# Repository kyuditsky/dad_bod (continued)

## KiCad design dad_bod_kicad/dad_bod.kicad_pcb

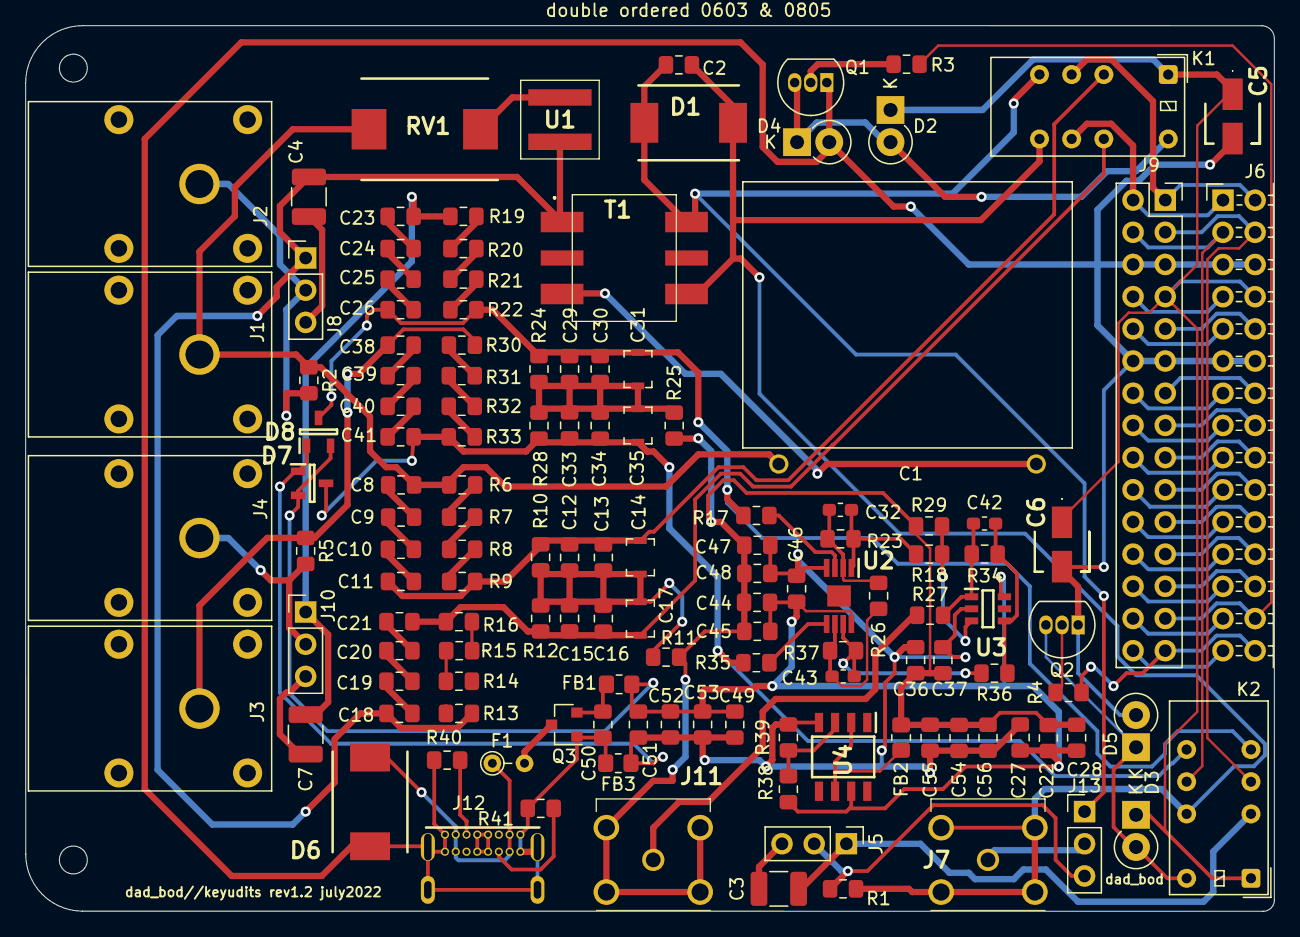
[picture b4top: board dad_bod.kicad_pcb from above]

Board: 2 copper layers, 98.5 x 69.9 mm, 133 parts (0 on the bottom side), 98 nets.

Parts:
C1: ECQ-UBAF474K; ECQ-UBAF474K-3_side
C2: 220pF; C_0805_2012Metric_Pad1.15x1.40mm_HandSolder
C3, C4, C7: 86nF; C_1210_3225Metric_Pad1.33x2.70mm_HandSolder
C5, C6: CP; EEE1AA220WR
C8, C9, C10, C11, C18, C19, C20, C21, C23, C24, C25, C26, C38, C39, C40, C41: 4pf; C_0805_2012Metric_Pad1.15x1.40mm_HandSolder
C12, C13, C15, C16, C29, C30, C33, C34: 350pF; C_0805_2012Metric_Pad1.15x1.40mm_HandSolder
C14, C17, C31, C35: CTRIM; C_Trimmer_Voltronics_JQ
C22, C27, C28, C36, C37, C44, C45, C46, C47, C48, C49, C50, C51, C52, C53, C54, C55, C56: C_0805_2012Metric_Pad1.15x1.40mm_HandSolder
C32, C42, C43: C_0603_1608Metric_Pad1.05x0.95mm_HandSolder
D1: SMCJ918.0CA; DIONM7959X262N
D2, D3, D4, D5: 1N4001; D_DO-41_SOD81_P2.54mm_Vertical_KathodeUp
D6: SMCJ5.0A; littlefuseTVS
D7, D8: BAV199-TP; bav199_tp_SOT95P237X125-3N
F1: 2.5a Fuse; R_Axial_DIN0204_L3.6mm_D1.6mm_P2.54mm_Vertical
FB1, FB2, FB3: Ferrite_Bead; R_0805_2012Metric_Pad1.20x1.40mm_HandSolder
J1, J2, J3, J4: Conn_01x01; Banana_Jack_S_RA_73099
J5, J8, J10, J13: Conn_01x03_Male; PinHeader_1x03_P2.54mm_Vertical
J6: Conn_02x15_Odd_Even; PinHeader_2x15_P2.54mm_Horizontal
J7, J11: BNC5-J-P-GN-RA-BH2D; BNC5JPGNRABH2D
J9: Conn_02x15_Odd_Even; PinSocket_2x15_P2.54mm_Vertical
J12: USB4085-GF-A_REVA4; GCT_USB4085-GF-A_REVA4
K1, K2: EC2-5NU; Relay_DPDT_Kemet_EC2
Q1, Q2: 2N3904; TO-92_Inline
Q3: AO3401A; SOT-23
R1, R2, R5: 30M; R_0805_2012Metric_Pad1.15x1.40mm_HandSolder
R3, R4: 1k; R_0805_2012Metric_Pad1.15x1.40mm_HandSolder
R6, R7, R8, R9, R13, R14, R15, R16, R19, R20, R21, R22, R30, R31, R32, R33: 1M; R_0805_2012Metric_Pad1.15x1.40mm_HandSolder
R10, R12, R24, R28: 50k; R_0805_2012Metric_Pad1.15x1.40mm_HandSolder
R11, R25: DNP; R_0805_2012Metric_Pad1.15x1.40mm_HandSolder
R17, R18, R23, R26, R27, R29, R34, R35, R36, R37, R38, R39: R_0805_2012Metric_Pad1.15x1.40mm_HandSolder
R40, R41: 5.1k; R_0805_2012Metric_Pad1.15x1.40mm_HandSolder
RV1: VP4032K122R300; CAPPM10080X500N
T1: GT07-110-013; GT07110013
U1: SL1002A600SP
U2: LTC6269; SOP65P490X110-9N_LTC6269
U3: LTC6268; SOT95P280X100-6N_LTC6268
U4: LM7301; SOIC127P600X175-8NLM7301

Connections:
0: J6.16, J9.15
1: J6.18, J9.17
2: J6.20, J9.19
3: J6.22, J9.21
4: J6.24, J9.23
5: J6.26, J9.25
8: J6.15, J9.16
9: J6.17, J9.18
10: J6.19, J9.20
11: J6.21, J9.22
12: J6.23, J9.24
13: J6.25, J9.26
14: J6.27, J9.28
15: J6.29, J9.30
BNCin+: C3.2, J5.1, K2.3
CV6: J6.28, J9.27, R3.1
CV7: J6.30, J9.29, R4.1
DIVin1+: C7.2, C23.2, J10.1, R19.1
DIVin1-: C38.1, J3.1, R5.1, R30.2
DIVout1+: C26.1, C29.2, C30.2, C31.1, D8.3 (A/K), K2.5, R17.2, R22.2, R24.2
DIVout1-: C33.1, C34.1, C35.2, C41.2, D7.3 (A/K), K2.8, R28.1, R33.1, R35.2
DIVout2+: C11.1, C12.2, C13.2, C14.1, K1.3, R9.2, R10.2
DIVout2-: C15.1, C16.1, C17.2, C21.2, K1.10, R12.1, R16.1
GND: C5.2, C6.2, C50.1, D4.2 (A), D5.2 (A), D6.2, FB3.2, J6.5, J6.6, J6.11, J6.12, J9.5, J9.6, J9.11, J9.12, J12.A1 (GND), J12.A12 (GND), J12.B1 (GND), J12.B12 (GND), J12.P1 (SHELL), J12.P2 (SHELL), J12.P3 (SHELL), J12.P4 (SHELL), Q1.1 (E), Q2.1 (E), Q3.1 (G), R40.1, R41.2
GNDREF: C22.1, C28.1, C36.1, C37.1, C44.2, C45.2, C47.2, C48.2, C54.2, C55.2, C56.2, FB2.1, J11.2, J11.3, J11.4, J11.5, R11.1, R25.1, R29.1
unnamed: C1.2, T1.3 (DRIVE_3)
unnamed: C3.1, J5.3
unnamed: C4.1, J8.3
unnamed: C7.1, J10.3
unnamed: C8.1, C9.2
unnamed: C10.1, C11.2
unnamed: C9.1, C10.2
unnamed: C12.1, C13.1, C14.2, C15.2, C16.2, C17.1, R10.1, R11.2, R12.2
unnamed: C18.2, C19.1
unnamed: C19.2, C20.1
unnamed: C20.2, C21.1
unnamed: C23.1, C24.2
unnamed: C24.1, C25.2
unnamed: C25.1, C26.2
unnamed: C29.1, C30.1, C31.2, C33.2, C34.2, C35.1, R24.1, R25.2, R28.2
unnamed: C32.1, R18.2, R23.1, U2.1
unnamed: C32.2, R23.2, R26.2, U2.2 (-)
unnamed: C38.2, C39.1
unnamed: C39.2, C40.1
unnamed: C40.2, C41.1
unnamed: C42.1, R27.2, R34.1, U3.1
unnamed: C42.2, R34.2, R36.1, U3.4 (-)
unnamed: C43.1, R36.2, R37.1, U2.7
unnamed: C43.2, R26.1, R37.2, U2.6 (-)
unnamed: C50.2, FB1.2, Q3.2 (S)
unnamed: D2.2 (A), D4.1 (K), K1.12, Q1.3 (C)
unnamed: D3.2 (A), D5.1 (K), K2.12, Q2.3 (C)
unnamed: D6.1, F1.1, J12.A4 (VBUS), J12.A9 (VBUS), J12.B4 (VBUS), J12.B9 (VBUS)
unnamed: FB2.2, U4.2 (-), U4.6
unnamed: J2.1, J8.2, R2.2
unnamed: J7.1, J13.2
unnamed: J4.1, J10.2, R5.2
unnamed: J11.1, R27.1
unnamed: J12.A5 (CC1), R40.2
unnamed: J12.A6 (DP1), J12.A7 (DN1), J12.B6 (DP2), J12.B7 (DN2)
unnamed: J12.B5 (CC2), R41.1
unnamed: Q1.2 (B), R3.2
unnamed: Q2.2 (B), R4.2
unnamed: R6.2, R7.1
unnamed: R7.2, R8.1
unnamed: R8.2, R9.1
unnamed: R13.1, R14.2
unnamed: R14.1, R15.2
unnamed: R15.1, R16.2
unnamed: R17.1, U2.3 (+)
unnamed: R18.1, R29.2, U3.3 (+)
unnamed: R19.2, R20.1
unnamed: R20.2, R21.1
unnamed: R21.2, R22.1
unnamed: R30.1, R31.2
unnamed: R31.1, R32.2
unnamed: R32.1, R33.2
unnamed: R35.1, U2.5 (+)
unnamed: R38.1, R39.1, U4.3 (+)
unnamed: RV1.1, U1.1
PLCin+: C4.2, C18.1, J8.1, R13.2, T1.1 (DRIVE_1), U1.2
PLCin-: C1.1, C8.2, J1.1, R2.1, R6.1, RV1.2
PLCout+: C2.2, D1.1, J13.1, K1.5, T1.6 (GATE_3)
PLCout-: C2.1, D1.2, J7.2, J7.3, J7.4, J7.5, K1.8, K2.10, R1.1, T1.4 (GATE_1)
V+: F1.2, Q3.3 (D)
VCC: C22.2, C27.1, C28.2, C44.1, C45.1, C46.2, C49.2, C51.2, C52.2, C53.2, D7.2 (K), D8.2 (K), FB1.1, R38.2, U2.8 (V+), U3.6 (V+), U4.7 (V+)
bnc_imp+: J5.2, J13.3, R1.2
dad_V-: J6.7, J9.8
greg: C27.2, C36.2, C37.2, C46.1, C47.1, C48.1, C49.1, C51.1, C52.1, C53.1, C54.1, C55.1, C56.1, D7.1 (A), D8.1 (A), FB3.1, R39.2, U2.4 (V-), U3.2 (V-), U4.4 (V-)
relaypwr: C5.1, C6.1, D2.1 (K), D3.1 (K), J6.8, J9.7, K1.1, K2.1
scope1+: J6.2, J9.1, K1.4
scope1-: J6.1, J9.2, K1.9
scope2+: J6.4, J9.3, K2.4
scope2-: J6.3, J9.4, K2.9
trigger1: J6.14, J9.13
trigger2: J6.13, J9.14
waveform1: J6.10, J9.9
waveform2: J6.9, J9.10

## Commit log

2022-02-11 Added readme.md & .gitignore
2022-02-11 Imported HPF, added divider, dad IO, & relay
2022-02-11 Corrected hpf scheme, added pass throughs on the dad io, changed j1/j2 inputs
2022-02-13 Reworked voltage divider, added attenuation simulation schematic
2022-02-23 Altered voltage divider section & added simulation circuit
2022-03-24 Added differential schematic & associated symbols & footprints, no values, ready for initial layout
2022-04-05 Added pcbNew files, block layouts complete
2022-04-18 changed some layout, realized it needs some rework, but versioning for posterity
2022-04-18 End of day, layout reworked. Mostly ready to route
2022-06-07 reworked layout
    To begin routing
2022-06-08 Routed PCB, layout needs rework, forked to dad_bod
2022-06-08 fixing scheme & pcb disparities
2022-06-08 new layout
2022-06-08 Routed board
2022-07-02 changed some routing/footprints after component selection
2022-07-05 swapped div1 & div 2 inputs, bnc in can be routed as plc out
2022-07-06 touch ups & final review
2022-08-10 Locally forked into dad_bod_kicad_v02
2022-08-24 Added sketches & iterations
2022-09-19 Added BOMs & db_standalone order
2022-10-05 Added scope screenshots from db_standalone_v01
2022-10-23 added standalone_v01 testing content
2022-11-30 Added beach_bod_01; Initial layout complete
2022-11-30 Layout Adjustments
2022-11-30 Initial Route
2022-11-30 Reworked ground plane & output opamp
2023-01-04 Added buds_diffprobe_spice and waveforms psu testing
2023-01-09 added beach_bod_02 & cleaned up file structure
2023-01-10 Routed beach_bod_02
2023-01-18 Version saving, added trimpot & BOM
2023-01-23 Added beach_bod_v02_cart
2023-02-27 Added v02 gerbers & testing notes
2023-02-27 Version saving, before rearranging relays
2023-03-14 Finished dad_bod_v02 layout, awaiting routing
2023-04-19 Added beach_bod troubleshooting video
2023-05-30 added notes to v02 after build
